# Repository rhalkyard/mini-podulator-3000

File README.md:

# Mini-Podulator 3000

External Mini-Podule carrier board for Acorn A3000 machines.

## Introduction

The Acorn A3000 is unique among Acorn's ARM systems in being able to accept both
an 8 bit "mini" expansion podules common to the A3010, A3020 and A4000 machines,
as well as a Eurocard-sized 16-bit podule as used by the rest of the Archimedes
and RiscPC range.

While the mini-podule fits internally, the standard podule slot on the A3000 is
merely exposed on the rear of the machine, able to accept a bare board but
clearly designed for an expansion enclosure of some kind. The mini-podule
interface is electrically identical to the standard podule interface, just with
an 8-bit data bus instead of 16 bit (and a couple of control lines omitted).
This carrier board is designed to act as a passive adapter allowing a second
mini-podule to be attached to the external podule connector.

## Why?

Because.

Though, more seriously, the main motivator for this is as an aid to developing
and testing hardware. My A3000 is my only Archimedes machine, and it does double
duty as both development environment and test rig. This carrier board will allow
me to experiment with a second mini-podule expansion card without sacrificing
the storage provided by my existing IDE mini-podule. Not to mention avoiding
having to leave the lid off!

## Compatibility

This carrier board is only really suitable for use with the A3000, as it is the
only machine with an external podule connector. It technically would fit in a
desktop system, but since it is shorter and wider (and with a minipodule
installed, taller) than a standard 100x160mm podule, it will not have mechanical
support and I do not recommend trying this.

## How to build

Order boards from your PCB fab house of choice. Solder components to board. It
shouldn't be too hard to figure out.

J1 is a 96-position DIN 41612 Eurocard connector, right-angle, board mount, with
male pins. Only rows A and C (i.e. 64 of the 96 pins) are used, but a 3-row
connector will also fit. Something like [Amphenol
86094647113745ELF](https://www.digikey.com/en/products/detail/amphenol-cs-fci/86094647113745ELF/5203923)
should do the job.

J2-J5 are generic 0.1"-pitch pin sockets. J2 and J5 are 1x17 pin, J3 and J4 are
1x5 pin.

J6-J9 are optional 0.1" pin headers to allow connection of logic analyser probes
for debugging. Leave them out if you want.

## To-do

Mini-podules need to be supported at the back panel. The mounting holes on the
rear edge of the carrier board are intended for some kind of bracket that
provides mechanical support to both the podule and the carrier board. Not sure
exactly what form this will take, but some kind of 3D-printed contraption would
work well here. Watch this space.

## (Lack of) warranty

I hope it goes without saying, but building something like this does come with
risks - you are exposing the sensitive internals of the computer to the
cruelties of the outside world.

If you take sensible ESD precautions and avoid shorting anything out, it should
be fine, but if you do manage blow up your machine with this, don't say I didn't
warn you.

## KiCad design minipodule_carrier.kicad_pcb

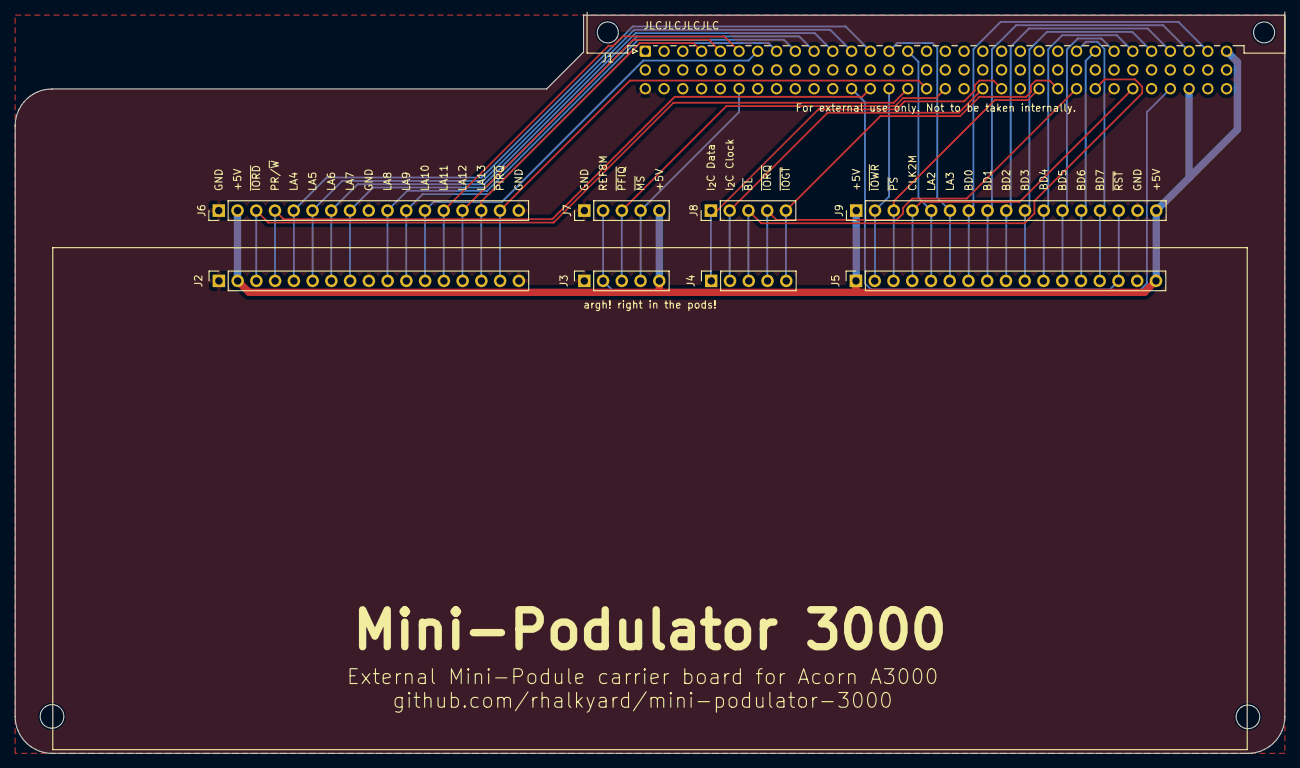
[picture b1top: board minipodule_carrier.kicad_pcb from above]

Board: 2 copper layers, 172.0 x 100.0 mm, 11 parts (0 on the bottom side), 37 nets.

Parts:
H1, H2: MountingHole; MountingHole_3.2mm_M3
J1: DIN41612_02x32_AC; DIN41612_C_3x32_Male_Horizontal_THT
J2, J5: Conn_01x17_Socket; PinSocket_1x17_P2.54mm_Vertical
J3, J4: Conn_01x05_Socket; PinSocket_1x05_P2.54mm_Vertical
J6, J9: Conn_01x17_Socket; PinHeader_1x17_P2.54mm_Vertical
J7, J8: Conn_01x05_Socket; PinHeader_1x05_P2.54mm_Vertical

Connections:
+5V: J1.a32, J1.c30, J2.2, J3.5, J5.1, J5.17, J6.2, J7.5, J9.1, J9.17
/BD0: J1.a31, J5.7, J9.7
/BD1: J1.a30, J5.8, J9.8
/BD2: J1.a29, J5.9, J9.9
/BD3: J1.a28, J5.10, J9.10
/BD4: J1.a27, J5.11, J9.11
/BD5: J1.a26, J5.12, J9.12
/BD6: J1.a25, J5.13, J9.13
/BD7: J1.a24, J5.14, J9.14
/CLK2: J1.c27, J5.4, J9.4
/I2C_CLK: J1.c19, J4.2, J8.2
/I2C_DAT: J1.c20, J4.1, J8.1
/LA2: J1.a15, J5.5, J9.5
/LA3: J1.a14, J5.6, J9.6
/LA4: J1.a13, J2.5, J6.5
/LA5: J1.a12, J2.6, J6.6
/LA6: J1.a11, J2.7, J6.7
/LA7: J1.a10, J2.8, J6.8
/LA8: J1.a9, J2.10, J6.10
/LA9: J1.a8, J2.11, J6.11
/LA10: J1.a7, J2.12, J6.12
/LA11: J1.a6, J2.13, J6.13
/LA12: J1.a5, J2.14, J6.14
/LA13: J1.a4, J2.15, J6.15
/PR/~W: J1.c13, J2.4, J6.4
/REF8M: J1.c29, J3.2, J7.2
/~BL: J1.c25, J4.3, J8.3
/~IOGT: J1.c23, J4.5, J8.5
/~IORD: J1.c15, J2.3, J6.3
/~IORQ: J1.c24, J4.4, J8.4
/~IOWR: J1.c14, J5.2, J9.2
/~MS: J1.c6, J3.4, J7.4
/~PFIQ: J1.c17, J3.3, J7.3
/~PIRQ: J1.c16, J2.16, J6.16
/~PS: J1.c22, J5.3, J9.3
/~RST: J1.c12, J5.15, J9.15
GND: J1.a1, J1.c1, J1.c3, J1.c4, J1.c26, J2.1, J2.9, J2.17, J3.1, J5.16, J6.1, J6.9, J6.17, J7.1, J9.16
